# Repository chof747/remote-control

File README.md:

Home Automation Remote Control
==============================

This project contains the hardware schematics and the firmware code for the Home Automation remote control.

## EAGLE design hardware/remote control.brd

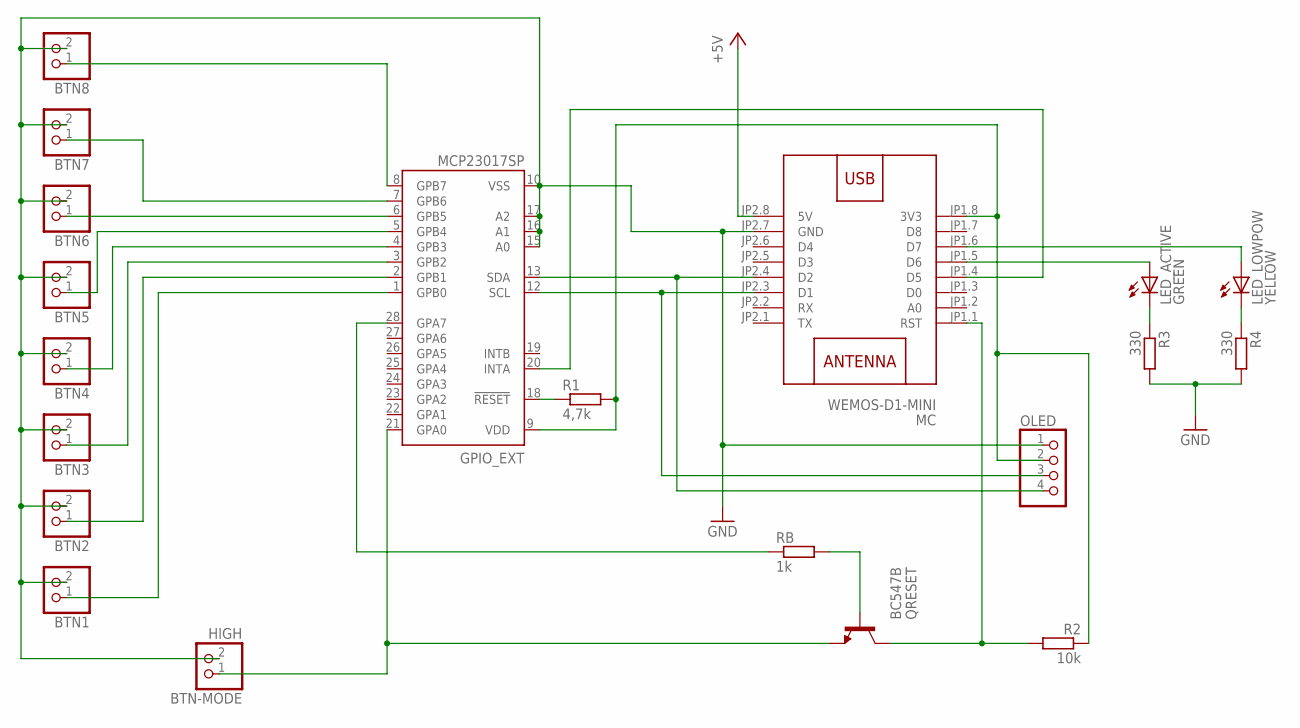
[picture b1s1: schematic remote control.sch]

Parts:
BTN1, BTN2: HIGH; 1X02
BTN3, BTN4, BTN5, BTN6, BTN7, BTN8: PINHD-1X2; 1X02
BTN-MODE: HIGH; 1X02
GPIO_EXT: MCP23017SP; DIL28-3
LED_ACTIVE: GREEN; LED3MM
LED_LOWPOW: YELLOW; LED3MM
MC: WEMOS-D1-MINI
OLED: PINHD-1X4; 1X04
QRESET: BC547B; TO92
R1: 4,7k; 0204/5
R2: 10k; 0204/5
R3, R4: 330; 0204/5
RB: 1k; 0204/5

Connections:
+5V: MC.JP2.8 (5V)
GND: BTN1.2, BTN2.2, BTN3.2, BTN4.2, BTN5.2, BTN6.2, BTN7.2, BTN8.2, BTN-MODE.2, GPIO_EXT.10 (VSS), GPIO_EXT.15 (A0), GPIO_EXT.16 (A1), GPIO_EXT.17 (A2), MC.JP2.7 (GND), OLED.1, R3.2, R4.2
unnamed: BTN-MODE.1, GPIO_EXT.21 (GPA0), QRESET.1 (E)
unnamed: GPIO_EXT.20 (INTA), MC.JP1.4 (D5)
unnamed: MC.JP1.1 (RST), QRESET.3 (C), R2.2
unnamed: GPIO_EXT.28 (GPA7), RB.1
unnamed: QRESET.2 (B), RB.2
unnamed: LED_ACTIVE.A, MC.JP1.5 (D6)
unnamed: LED_ACTIVE.K (C), R3.1
unnamed: LED_LOWPOW.K (C), R4.1
unnamed: LED_LOWPOW.A, MC.JP1.6 (D7)
PIN1: BTN1.1, GPIO_EXT.1 (GPB0)
PIN2: BTN2.1, GPIO_EXT.2 (GPB1)
PIN3: BTN3.1, GPIO_EXT.3 (GPB2)
PIN4: BTN4.1, GPIO_EXT.4 (GPB3)
PIN5: BTN5.1, GPIO_EXT.5 (GPB4)
PIN6: BTN6.1, GPIO_EXT.6 (GPB5)
PIN7: BTN7.1, GPIO_EXT.7 (GPB6)
PIN8: BTN8.1, GPIO_EXT.8 (GPB7)
RST_MCP: GPIO_EXT.18 (!RESET), R1.1
SCL: GPIO_EXT.12 (SCL), MC.JP2.3 (D1), OLED.3
SDA: GPIO_EXT.13 (SDA), MC.JP2.4 (D2), OLED.4
VDD: GPIO_EXT.9 (VDD), MC.JP1.8 (3V3), OLED.2, R1.2, R2.1

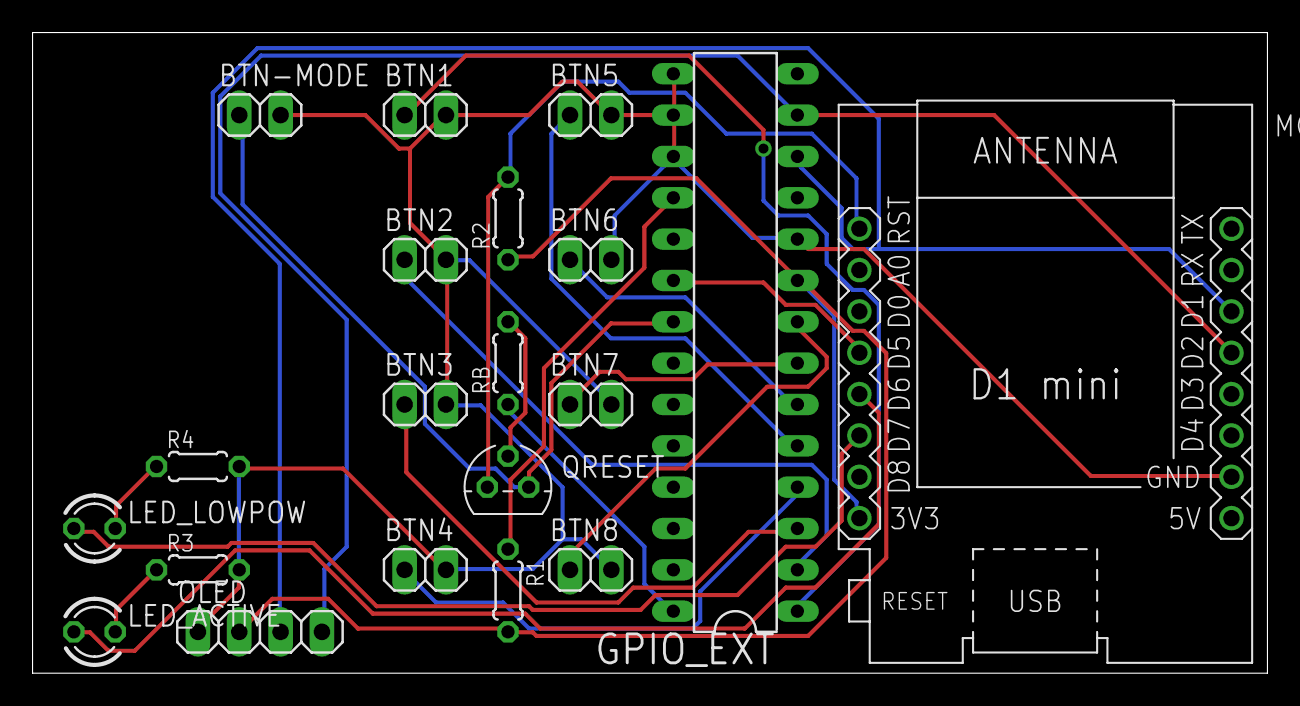
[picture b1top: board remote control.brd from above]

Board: 2 copper layers, 75.9 x 39.4 mm, 20 parts (0 on the bottom side), 22 nets.

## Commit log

2020-08-05 start with git-ignore
2020-08-05 Initial commit after first version implemented
2020-08-05 corrected type with #define WIFI_SSID
2020-08-06 Moved config.h, config.sample.h to include folder
2020-08-06 wifi and mqtt take config from config.h
2020-08-06 Added prebuild script to have name and version
2020-08-11 Added display and mode controller
    - Added basic display functionality
    - Added ModeController base class
    - Added RemoteControl mode controller
    - Created mode registry and integrated mode switching into firmware main.cpp
2020-08-27 Changes to firmware:
    - added sensor module
    - Structured modes differently
    - Added mqtt information on device
2020-08-27 Adapted git-ignore
2020-08-29 restructured startup - added safeguard for connection error - restructured routines in source code
2020-08-29 Improved design of MQTT module
    - Added topics for telemetry and commands
    - changed return type of reconnectMQTT() to enable actions on failed connection
2020-08-30 Changed workspace settings to add also a test project
2020-08-30 Corrected missing update of display
2020-08-30 Refactoring of sensor list obtaining
    Preparation to enable storing sensors within the EEPROM of ESP8266 in
    order to be able to retrieve sensor information quicker
    - Moved setup of a sensor based on the provided line to its own method
    - added forcing of reread of sensor parameter to Obtain sensor method
2020-09-03 changed way sensor gets data
2020-10-16 Adjusted for production
2020-10-18 Changed version and name description
    for firmware module prep.
2020-10-18 Firmware Module and MQTT change
    - moved the handling of MQTT messages to the modules
    - added firmware module which handles status information
    - added conditional compilation for interrupt clearanse (to allow bare Wemos D1 as prototype)
2020-10-19 Corrected main.cpp - from prototyping
2020-10-19 Implemented OTA Update
2020-10-23 Updated config_sample.h to the new settings
2020-10-23 removed serial printing from prod environment
2020-10-23 Changed error messages fro OTA upload
2020-10-23 Added loop event for modes
    - The main loop calls the loopMode function of the mode registry
    - Each mode new onLoop event gets called by the loop
    - The loop is called not every time but every number of loop cycles defined by the MODE_LOOP_CYCLE constant in config.h
2020-10-23 Added the battery check to the onLoop function
2020-10-23 Changed Upgrade behaviour analog to tasmota
2020-10-28 Fixed issue with sensor scrolling
2020-10-28 New version - with firmware info
2020-10-28 Changed sensor welcome message
2020-10-28 Added ask for update button (BTN10) to pull update
2020-11-08 Added Upload functionality by Button
2020-11-08 removed unecessary include from mqtt.cpp
2020-11-08 Added new WifiManager
2020-11-08 Removed old WiFi Manager
2020-11-21 Added error output on WLAN and MQTT issues
    - added error function which prints the error and restarts or goes to sleep
    - reduced retries with MQTT connection to three
    - added constant for error printing time
    - added error printing for WLAN connection failure
2020-11-27 intermediate commit
2021-02-21 Changed sensor value retreival
    - Removed storing of sensors in array
    - Used new web call to nodered instance which cycles through values on server side
2021-02-21 Changed to 4 line display with smaller fonts
2021-02-21 Adapted config_sample
2021-03-11 Added OTA scripts for automated deployment
2021-03-11 Git Ignore for OTA scripts
2021-03-11 Added new OTA mode into software and fixed interrupt issue
2021-11-14 temporary
2021-11-16 moving old stuff out of the way
2021-11-25 First new structure including remote function
    - Reorganized module in the new form
    - Added display, button controlls and wifi + mqtt
    - Added remote controller and timeouts
    - Added individual timer to timout controller
    - Implemented stub for idle controller
    - Button presses are shown on the display
2021-11-25 Added mvp functionality:
    - Remote mode is completed with 19 button options (10 serves as shift)
    - Added idle controller switching into deepsleep
    - completed display
    - added mqtt messages for deep sleep and buttons
2021-12-04 changed to real production system
2021-12-04 Added Status Component
    - Added led control for green and yellow led
    - Added error catching for mqtt and wlan
    - Changed return type of setup for component to bool to indicate failure
    - main routine reacts on failures
2021-12-04 use print message constant for remote controller
2021-12-05 Encapsulated display update in its own routine (show())
2021-12-05 Added wifi connection status at startup to display
2021-12-16 Added device data controller and bat status
    - Added device data controller files
    - Added battery level management to status component
    - added device data controller after remote controller
    - added battery management constants to config.h
2021-12-17 Setup OTA functionality
    - added OTA component
    - created handlers for start, end and progress
    - added OTA component
    - added special upload mode in device controller which is stopping the timeout
2021-12-18 Removing old firmware
2021-12-18 removed ota folder
2022-03-30 Added docker configuration for testing with hass
2022-04-01 changed settings
2022-04-01 Added custom conmponents path to test setup
    - added custom components directory mapping to docker compose file
    - added environment file
    - added .env to .gitignore
2022-04-01 Start of sensor implementation via websockets
    - Added websocket component to talk to home assistant - able to:
    - receive messages
    - log on to Home Assistant with API key
    - Added websocket message classes

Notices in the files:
parts and their libraries:
diy-modules: Released under the Creative Commons Attribution 4.0 International License: http://creativecommons.org/licenses/by/4.0
